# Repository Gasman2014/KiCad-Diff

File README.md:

# KiCad-Diff

This is a Python program that compares revisions of KiCad PCBs.

The layers of a KiCad board are exported to SVG, and the output is presented as a gallery of images on a web page. Each layer pair can be compared, and the combined view clearly highlights where the layers differ from one another.

The diff output can be scrolled and zoomed in and out for closer inspection. The pair of "before and after" views will also pan and zoom together.

## Instructions

### Dependencies

- Ensure that you have Python3 installed. Why? https://www.pythonclock.org
- Python Libraries from Kicad 5.* or 6.*
- For extra python dependencies check the `requirements.txt`

#### wxWidgets

_On macOS_ using Apple sillicon, you should export these flags first
```bash
export CFLAGS=-I/$(brew --prefix)/include
export CXXFLAGS=-I/$(brew --prefix)/include
```

_On Ubuntu_, wxWidgets can be installed with:
```bash
sudo apt install python3-wxgtk4.0
```

#### Installing dependencies

```bash
cd KiCad-Diff
pip3 install -r requirements.txt
```

## Usage

Make sure you have SCMs (Git, Fossil and/or SVN) available through the PATH variable.
Add the script path to your PATH too so the `kidiff` and `plot_kicad_pcb` will be available.
This can be done easily with:

```bash
cd KiCad-Diff
source env.sh
```

The terminal should give you some useful information on progress. Please include a copy of the terminal output if you have any issues.

### Command line help

```bash
usage: kidiff [-h] [-a COMMIT1_HASH] [-b COMMIT2_HASH] [-g] [-s SCM] [-d DISPLAY] [-p PORT] [-w] [-v] [-o OUTPUT_DIR] [-l] [-f] [PCB_PATH]

Kicad PCB visual diffs.

positional arguments:
  PCB_PATH              Kicad PCB path

optional arguments:
  -h, --help            show this help message and exit
  -a COMMIT1_HASH, --commit1-hash COMMIT1_HASH
                        Commit 1 hash
  -b COMMIT2_HASH, --commit2-hash COMMIT2_HASH
                        Commit 2 hash
  -g, --gui             Use gui
  -s SCM, --scm SCM     Select SCM (git, svn, fossil)
  -d DISPLAY, --display DISPLAY
                        Set DISPLAY value, default :1.0
  -p PORT, --port PORT  Set webserver port
  -w, --webserver-disable
                        Does not execute webserver (just generate images)
  -v, --verbose         Increase verbosity (-vvv)
  -o OUTPUT_DIR, --output-dir OUTPUT_DIR
                        Set output directory. Default is '.kidiff'.
  -l, --list-commits    List commits and exit
  -f, --frame           Plot whole page frame

```

### Usage examples

```bash
# With a Git repo
kidiff led_test.kicad_pcb

# Forcing an specific SCM when more than one is available (Precedence: Git > Fossil > SVN)
kidiff led_test.kicad_pcb --scm fossil

# With a SVN repo, passing commit 1 and 2 on the command line
kidiff led_test.kicad_pcb -a r1 -b r3
```

## Debugging

There should be some output in the launch terminal. Please copy this and include it in any issues posted. If the program is not working, please check that you can run the `plot_kicad_pcb` routine directly by invoking it from the command line and passing the name of the `*.kicad_pcb` file.

```bash
plot_kicad_pcb board.kicad_pcb
```

# Screenshots

<p align="center">
  
  <br>
  Commits Selection
  <br>
</p>

<p align="center">
  
  <br>
  Gallery View
  <br>
</p>

<p align="center">
  
  <br>
  Triptych view
  <br>
</p>

<p align="center">
  
  <br>
  Attributes Diff
  <br>
</p>

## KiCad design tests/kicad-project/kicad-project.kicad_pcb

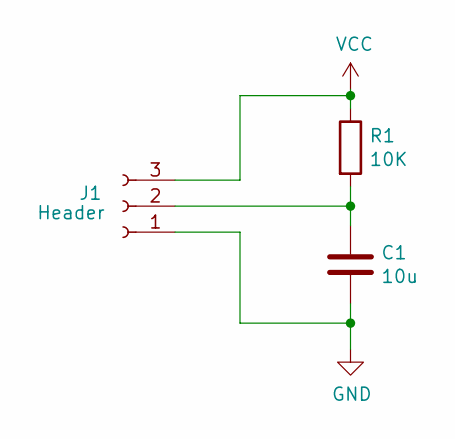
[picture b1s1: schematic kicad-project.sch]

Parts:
C1: 10u; CP_Radial_D4.0mm_P1.50mm
J1: Header; PinHeader_1x03_P2.54mm_Vertical
R1: 10K; R_Axial_DIN0204_L3.6mm_D1.6mm_P5.08mm_Horizontal

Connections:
GND: C1.2, J1.1
unnamed: C1.1, J1.2, R1.2
VCC: J1.3, R1.1

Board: 2 copper layers, 3 parts (0 on the bottom side), 3 nets, no tracks yet.

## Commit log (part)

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2017-08-16 Update README.md
    Adjust screenshot settings
2017-08-16 Minor edits to replace git references .
2017-08-17 Update screenshots and minor edit to colour of triptych_diff1 background (red to green)
2017-08-17 Round colour dot
2017-08-21 Updated css Tidied up Kidiff.sh Moved changes fro _wc (working copy) to kidiff.sh Working on Kidiff_wc.sh to support cascading style sheet sheet.css
2017-08-21 kidiff_wc now working. Committed prior to trying to move whole structure to web directory.
2017-08-23 Reworked for more comprehensive range of plots - now does all layers including two inner copper layers. Very easy to add more layers. Also early version of text diff - this is surprisingly difficult 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
    New css based system and some initial work at putting some board stats on
    the front page. Presently have to copy .css manually.
2017-08-23 Major update to plot generation - now produces coloured output depending on layer and plots are now negatives. Major update to web generation process and web page layouts.
2017-08-25 Updated repo with new screen shots
2017-08-25 Forgot to re-add readme
2017-09-01 Added initial command line options (h, v & q). Addressed an error where using tr -d 'strg' to trim a search string caused a strange error and deleted all 'd's in the VERSION string. Addressed an erro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
2017-09-01 Minor tidying of repo
2017-09-25 Updated install instructions & warning re versions
    Add imagemagick install instructions & warning re September nightly incompatibility
2017-11-30 Tidy
2018-06-04 Initial attempt at GUI version
    Initial GUI version supporting Git, SVN & Fossil (basic autodetect).
    Still WIP
    diff versions from PcbDraw with KiCadDiff processing.
2018-10-04 Add missing tkui.py file
    Added missing tkui.py file. Minor edit to path.
2018-10-04 Add plotPCB2.py
2018-10-04 Updated read me with instructions
2018-10-04 Add .pyc to gitignore
2018-10-13 Suggested changes to html header
2019-01-29 Add initial pdf formatting for QL700 labels
2019-02-19 Multiple fixes and enhancements
2019-05-18 Added new SVG branch. Note TKui now needs to have the layers and resolution either removed or managed in the new code. The revision selection works
2020-03-01 Incorporated svg-pan-zoom in main window. Needed to add Python webserver to permit svg-pan-zoom to work in subsidiary windows. Still issues about filter coloring entire paired window div
2020-03-02 Added SCM detection logic and list configured SCMs in splash screen
2020-03-02 Updated screenshots and README. Reordered SCM priority
2020-03-03 Further minor tweaks/typo corrections to README.md
2020-03-07 Separate plotPCB versions for macOS and other *nix. Minor edits and some debugging advice. Typos correction.
2020-03-16 Incorrect layer call on non-macos version.
2020-03-21 Corrected plot path error
2020-04-27 Missing import and graphics directive added
2020-04-27 Correct board directive on macOS too
2020-05-27 Remove `_escape_string` call from `kidiff_gui` #11
2020-05-27 Soft code the path to plotPCB.py
    Add error reporting for the calls to plotCmd
2020-05-30 Initial script to add tools to the path
2020-05-30 Add a flag to disable webserver
2020-05-30 Minor fix when using GUI
2020-05-30 Update formatting
2020-05-31 Remove --gui option in favor of checking need
    Fix incorrect comparison for args.commit{1,2}
    Move gui handling into getProject function
    Remove defaults for args.commit{1,2}
    Make args.kicad_pcb parameter optional
    Call getProject on emtpy args.kicad_pcb
    Fill single emtpy args.commit{1|2} with hash of HEAD commit
2020-08-22 fix name splitting
2020-09-22 Update message
2020-09-22 Format a little bit better to be understandable
2020-09-22 Update documents folder
2020-09-22 Update plotPCB usage and add more layers
2020-09-22 Update plotPCB usage
2020-09-22 Rename kidiff to be a single program
2020-09-22 Revert renameing
2020-09-23 Update usage
2020-09-23 Enable escape (Esc key) to exit from the window
2020-09-30 Add more labels and make it quiet when needed
2020-09-30 Many minor user-friendly improvements
2020-09-30 Make it flexible for multiple Kicad projects inside a GIT repository. Extra changes still needed for other SCMs.
2020-09-30 Fix typo on folder name
2020-09-30 Fix error with plotpcb not printing valid data and move the CSS to a file
2020-09-30 Remove whitespace
2020-09-30 Move all SCM code to external files
2020-09-30 Fix 'readlink -f' missing on OsX
2020-09-30 Update functions
2020-09-30 Overall improvements for SCM selection
2020-09-30 Set filebrowser to use current directory
2020-09-30 Hide hidden files in the filebrowser
2021-01-04 Automatically identify macOS or Linux to select proper plotPCB script. Replaced some repeated code with iterables. Cleanly shuts down webserver using ctrl+c. Defaults to generating files in a temp di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
2021-01-04 Consolidated Linux and macOS plotPCB scripts. os.path.join instead of hardcoded path separators (still need to do for svn and fossil functions). Consolidated some repeated blocks of code using iterat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
2021-01-27 Initial work to make auto detection of the SCM
2021-01-28 Improve SCM selection
2021-02-03 Fix fossil artifacts and info commands
2021-02-03 Remove wrong strip after run_cmd
2021-02-03 Remove unused tests folder
2021-02-03 Typo
2021-02-03 Simplify the way scms are executed
2021-02-03 Update commands
2021-02-03 Major update
    Major update to support multiple GIT repos [#20]. Rebases cose, splits out scm functions, seperates templating from code.
2021-02-03 Fix datetime variable
2021-02-03 Fix SVN, GIT and Fossil add log commands being used commands to make it easy to debug
2021-02-03 Fix paths and print commands
2021-02-03 Latest fix to work on all SCMs
2021-02-03 Adjust GUI images
2021-02-03 Update images
2021-02-03 Update image size
2021-02-03 Update image sizes
2021-02-03 Update title
2021-02-03 Start webserver without noise, also shows the url
2021-02-03 Clean SVN commit messages
2021-02-03 Update string
2021-02-04 Corrected path error. Artefacts were being generated in '.../-o/'.
2021-02-04 Correct paths for git diffs.
2021-02-07 Replaced missing line continuation backslash. Fixes [#30]
2021-02-12 Format debugging outputs
2021-02-14 Sanitize imports and clean up name space
    Import only needed need symbols and remove wildcards.
2021-02-15 Migrate SCM polymorphisms into classes
    The way the code was laid out can work but it is not "pythonic"; in
    Python, modules are not "first class citizen" and they can not be
    really manipulated like variables (some edge cases can bite you). It
    is safer to declare classes with static methods which will simply act
    as namespaces.
2021-02-20 kidiff: put common diff generation outside of the loop on layers
2021-02-20 Only call directly commands from the scripts without shell
    This removes all requirements for external utilities (shell, grep,
    perl,...) and bring the processing back into python.
    For svn, use the machine readable xml output for log.
    This change should provide similar functionality as what was done before.
2021-03-02 Improve HTML with title and a favicon
2021-03-02 Make it work with nested projects
2021-03-03 set foreground where background is explicitly set
2021-03-03 Use correct format for date in svn
    This should fix #41
2021-03-04 Git needs more characters to show the version
2021-03-04 Add instructions and python dependencies
2021-03-25 Generate duplicated images with the custom layer name from the board
2021-03-25 Avoid duplicate work
2021-03-31 Remove not used template file
2021-03-31 Organize and format html snippets
2021-03-31 Improve formating for humans
2021-04-01 Create LICENSE
    Add MIT Licence
2021-04-01 Fix 2nd image reference
2021-06-18 Update with extra modules
2021-06-18 Support Kicad >= 5.99
2021-06-18 Harden it when there are spaces in paths
2021-06-22 Fix version number on OSX. Disable prints with using -q flag and set missing default output folder.
2021-06-26 Add support to compare local not commited changes
2021-06-28 Bump pillow from 8.1.2 to 8.2.0
    Bumps [pillow](https://github.com/python-pillow/Pillow) from 8.1.2 to 8.2.0.
    - [Release notes](https://github.com/python-pillow/Pillow/releases)
    - [Changelog](https://github.com/python-pillow/Pillow/blob/master/CHANGES.rst)
    - [Commits](https://github.com/python-pillow/Pillow/compare/8.1.2...8.2.0)
    ---
    updated-dependencies:
2021-07-02 Improve print on OSX
2021-07-02 Improve layer color on Safari in triptych view, it is colored now
2021-07-02 Add quotes around URLs in HTML attributes
2021-07-02 Harden .svg filename parsing and improve image colors.
2021-07-02 Check if the board file exists and it is actually a .kicad_pcb
2021-07-02 Print commands as commands (easy debug)
2021-07-02 Remove prints for debug
2021-07-02 Change pages with right/left arrows
2021-07-02 Clean code to change page with keyboard, add space bar as shortcut to go back to home
2021-07-03 Check input file only for command line
2021-07-04 Cleanup
2021-07-04 Fix navigation for nested projects
2021-07-05 Added additional info to tryptych panel Summary Problem Solution Notes
2021-07-05 Improve css
2021-10-27 Fix kiplotpcb -> plotpcb command in readme
2021-10-28 Improve view on Kicad Nightly
2021-11-14 Fix various typos
    Found via `codespell -q 3`
2021-11-18 Add flag to allow changing output folder
2021-11-18 Allow to source tools from anywhere
2021-11-19 Adjust output dir for nested projects. Sane variables and functions.
2021-11-19 Move verbose move to up to cover all commands
2021-11-19 Add stdrr and stdout of the commands in the verbose mode
2021-11-20 Newer version of Kicad has path with name KiCad instead of Kicad
2021-11-20 Disable annoying warning on OSX
2021-11-22 Fix being able to use kidiff from anywhere
2022-01-16 Update paths for Kicad 6.0 on macos
2022-01-16 Disable exit when plotpcb returns since Kicad 6.0 is returning false always
2022-01-17 Add flag to list commits and exit
2022-01-17 Space bar how to homepage (fix)
2022-01-19 Replace TkInter with wxWidgets
2022-01-19 Add Kicad integration (PCM metadata and plugin)
2022-01-24 Workaround layout files so they will work on firefox too
2022-01-24 Remove extra echo
2022-01-24 Remove optimization flag. This is more like a temporary fix
2022-01-24 Improve script names
2022-01-25 Improve some issues
2022-01-25 By default generate kidiff folder inside repo folder (better)
2022-01-25 Avoid breaking when the webserver port is in use.
2022-01-27 Remove old unecessary env setup
2022-01-27 Drop pygubu dependency
2022-01-27 Improve images
2022-02-13 Rename file
2022-02-13 Remove tk dependency
2022-02-14 Improve terminal output and fix frame flag
2022-02-14 Use macos system's python
2022-02-14 Change order of events
2022-02-14 Improve output when plot_kicad_pcb does not return well
2022-02-14 Try to close app on macos
2022-02-14 Fix sed for macos
2022-02-14 Try to close app when dialog closes
2022-02-14 Update Gui
2022-02-17 Fix missing missing triptych folder
2022-02-23 Skip version if pcbnew does not have this attribute
2022-02-26 Workaround to fix the last file of the list that was not being included
2022-02-26 Add more svg tweaks
2022-02-26 Rename svg tweaks script
2022-02-26 Improve generated svgs
2022-03-09 Try to improve finding wx libraries on some macos
2022-05-10 Change svg precision and remove workaround
2022-06-27 Update kicad paths on macOS
2022-08-07 Fix holes (vias) appearing on all layers
2022-09-01 Format command
2022-09-07 Rever mistake
2022-09-10 Fix identation
2022-12-15 Normalize var style
2022-12-15 Increase precision to the max allowed for the browsers
2022-12-15 Use the full git hash instead of a short one that may fail on big repos
2023-01-19 Remove dateutil as the dependency
2023-01-19 Update python requirements
2023-01-19 Update, improving text, scripts and URL of images.
2023-01-19 Fix issues when author and/or msg is missing
2023-01-24 Plot schematics
2023-01-31 Update to list all schematics if there are more than one
2023-02-18 Find kicad-cli in the PATH
2023-02-18 Plot schematics if kicad-cli was found
2023-02-19 Skip sch export if the kicad_sch is missing
2023-02-19 Add info of the kicad v7 pcbs
2023-02-20 Add kicad-cli to the PATH for Kicad 7
2023-03-18 don't return when no difference
